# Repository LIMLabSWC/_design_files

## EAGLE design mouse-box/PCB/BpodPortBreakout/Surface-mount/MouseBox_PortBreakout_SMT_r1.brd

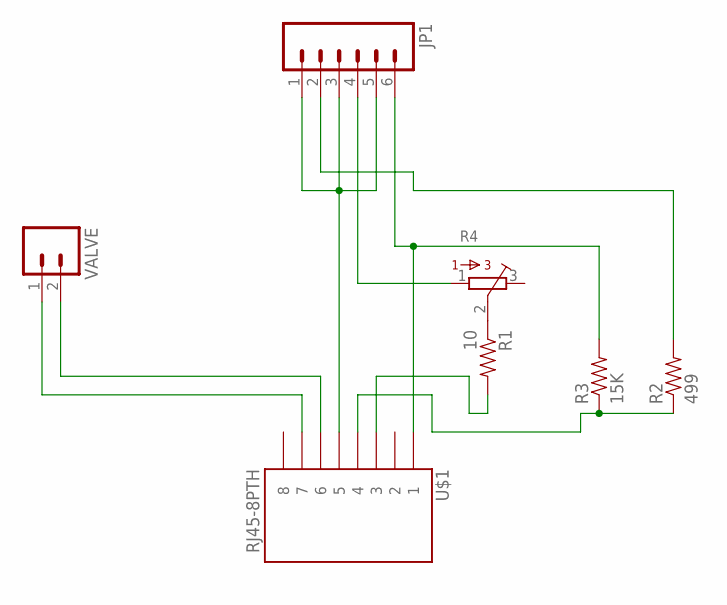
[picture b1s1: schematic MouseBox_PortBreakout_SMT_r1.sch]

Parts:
JP1: M063.5MM-6; SCREWTERMINAL-3.5MM-6
R1: 10; 1206
R2: 499; 1206
R3: 15K; 1206
R4: 3362R
U$1: RJ45-8PTH; RJ45-8
VALVE: M023.5MM_LOCK; SCREWTERMINAL-3.5MM-2_LOCK

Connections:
GND: JP1.1, JP1.3, JP1.5, U$1.5
unnamed: JP1.6, R3.2, U$1.1
unnamed: R2.1, R3.1, U$1.4
unnamed: JP1.2, R2.2
unnamed: R1.1, R4.2
unnamed: U$1.6, VALVE.2
unnamed: U$1.7, VALVE.1
unnamed: JP1.4, R4.1
unnamed: R1.2, U$1.3

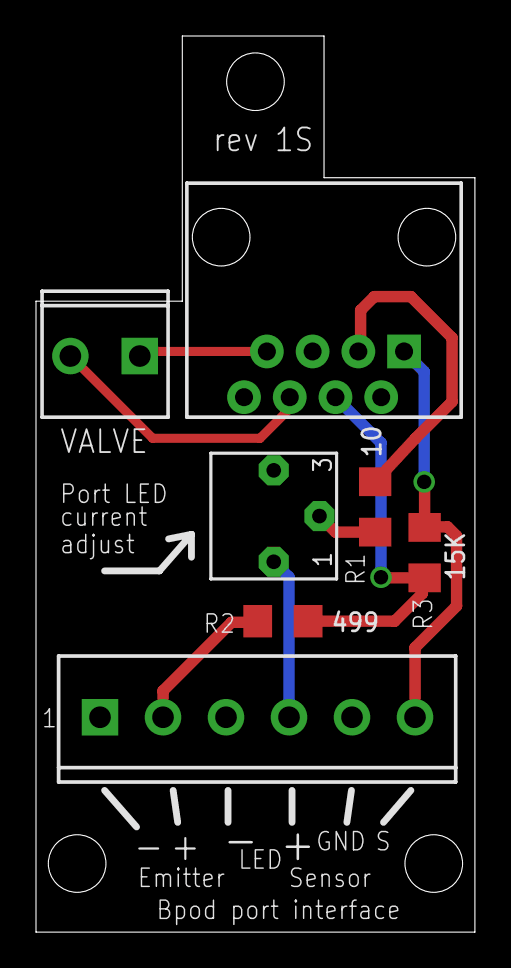
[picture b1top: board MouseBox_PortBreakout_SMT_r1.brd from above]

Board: 2 copper layers, 24.4 x 49.8 mm, 7 parts (0 on the bottom side), 9 nets.

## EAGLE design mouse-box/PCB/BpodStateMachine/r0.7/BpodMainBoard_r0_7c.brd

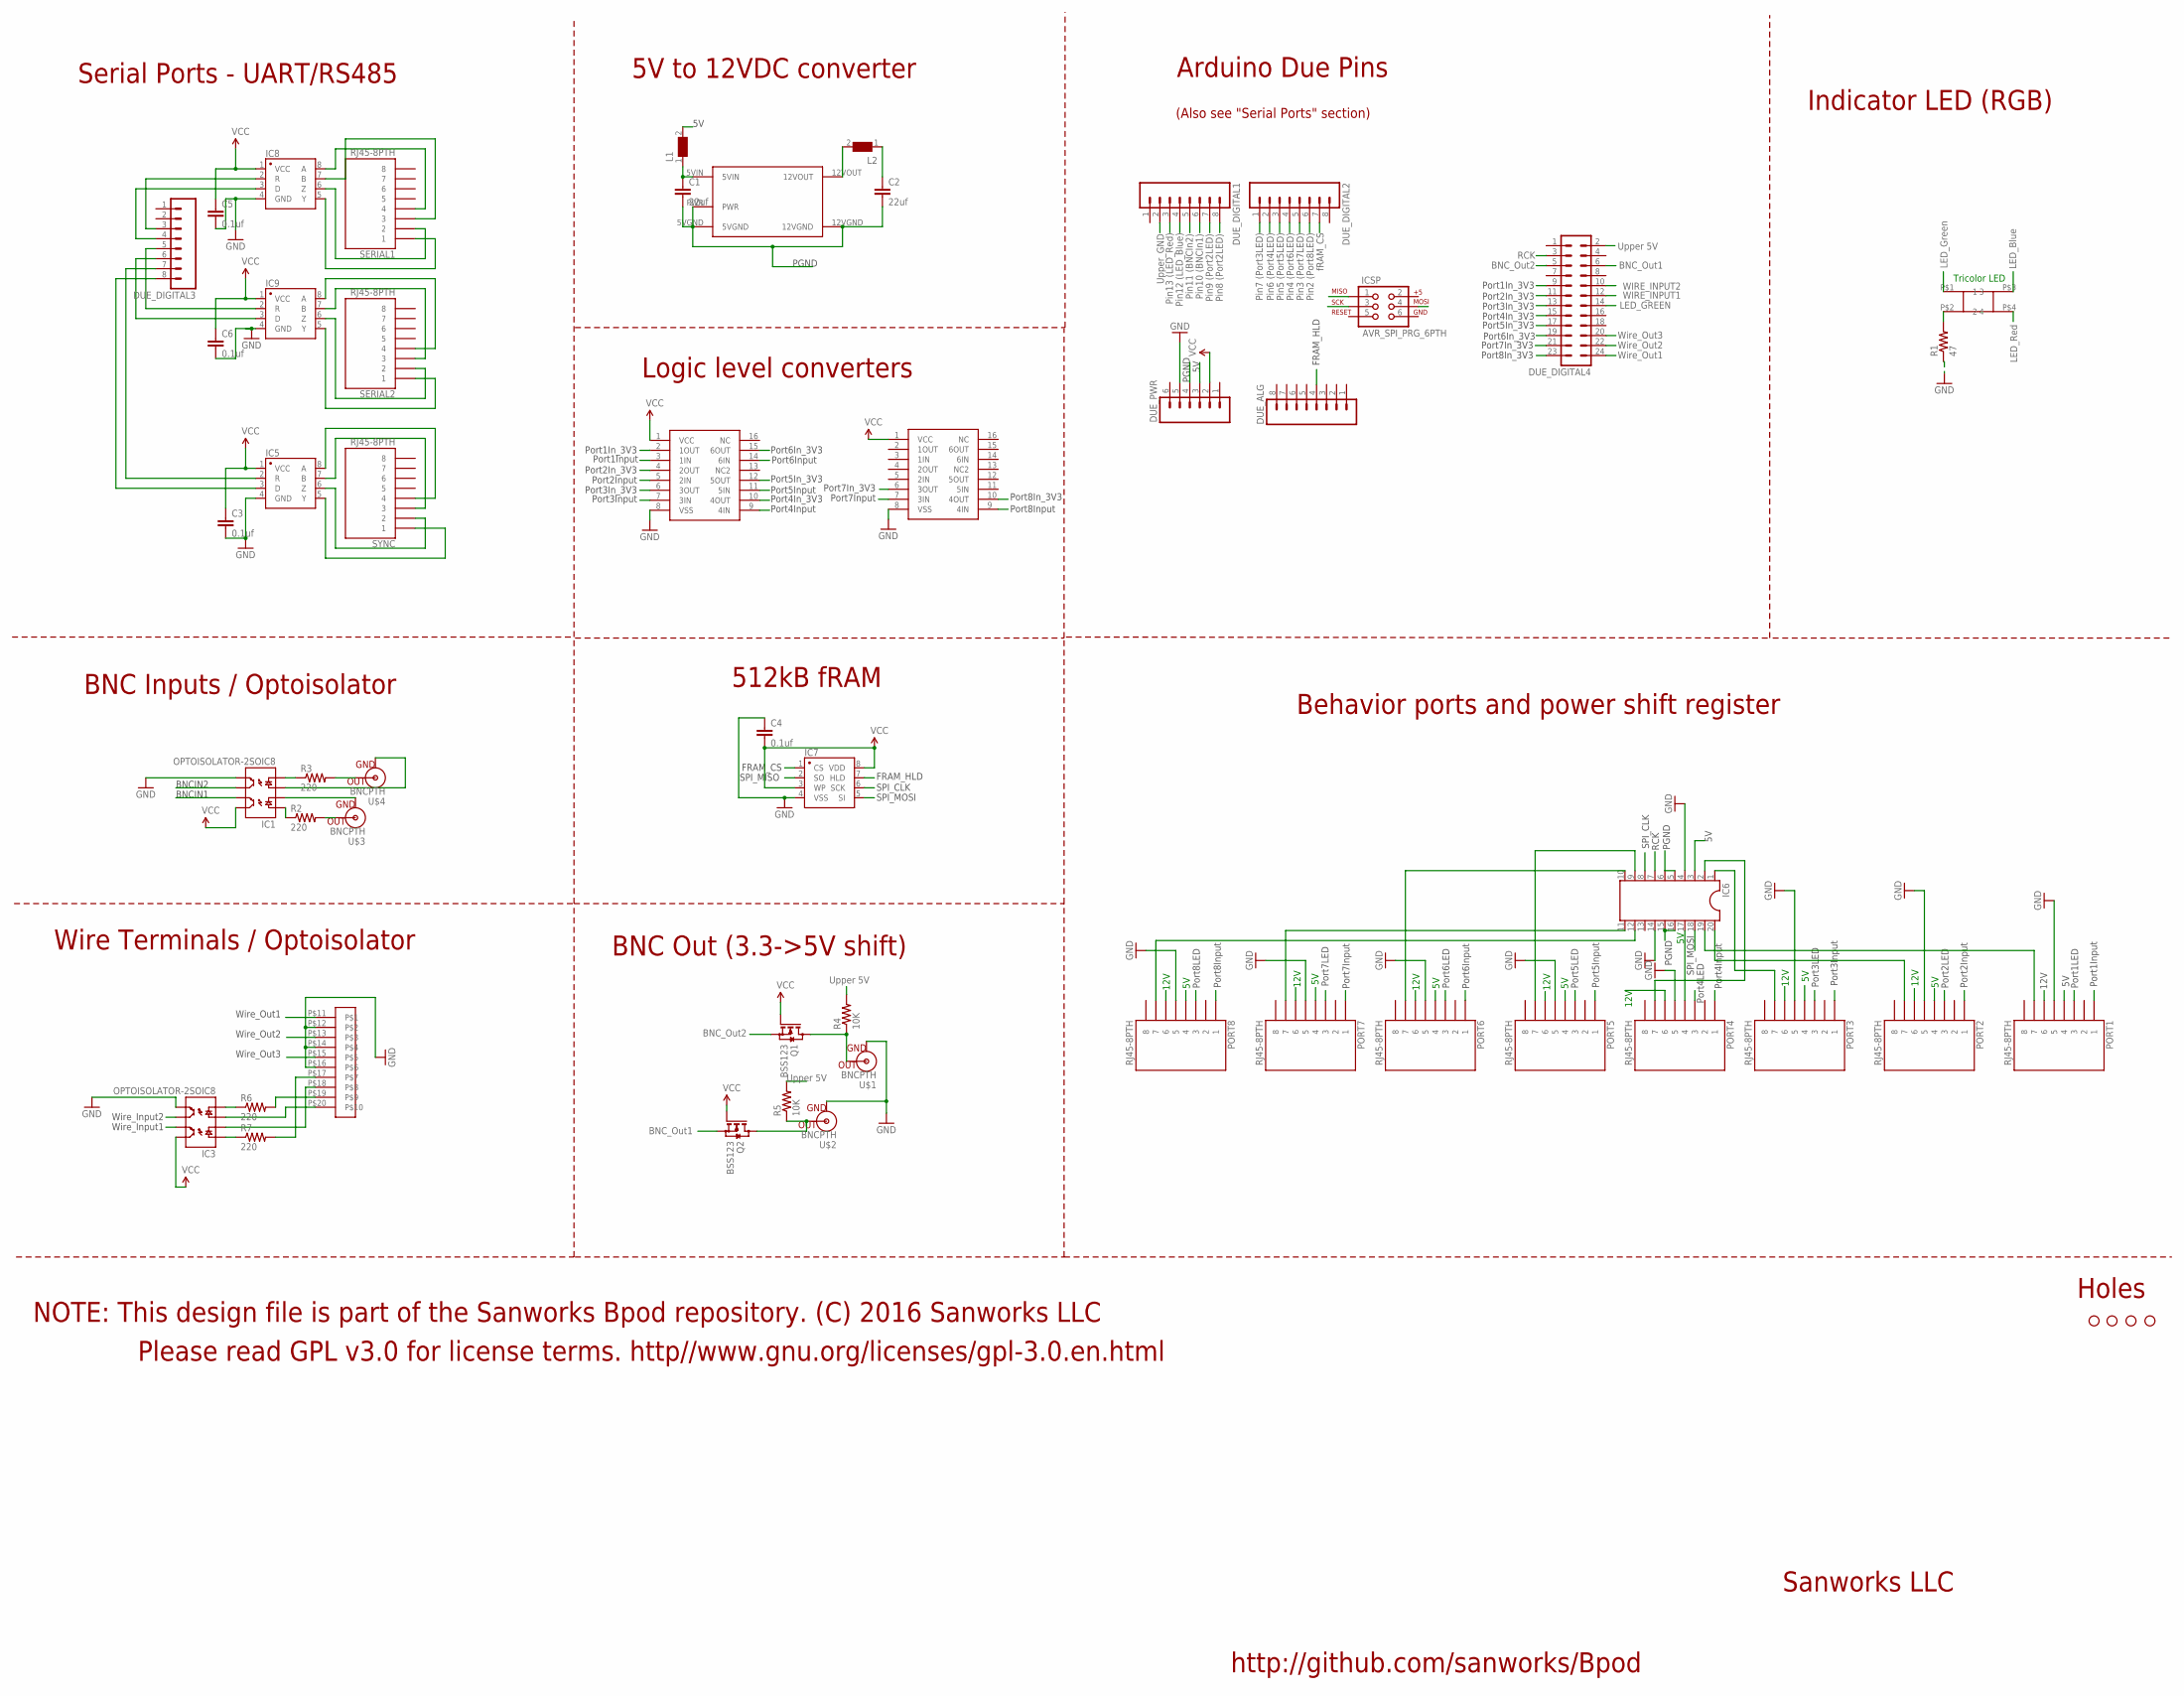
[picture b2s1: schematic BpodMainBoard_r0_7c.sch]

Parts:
C1, C2: 22uf; 1206
C3, C4, C5, C6: 0.1uf; 1206
DUE_ALG: M081X08; 1X08
DUE_DIGITAL1, DUE_DIGITAL2, DUE_DIGITAL3: M081X08; 1X08
DUE_DIGITAL4: MA12-2
DUE_PWR: M06SIP; 1X06
IC1, IC3: OPTOISOLATOR-2SOIC8; SO08-2
IC2, IC4: CD4050; SO16
IC5, IC8, IC9: SN65HVD31DR; SO08
IC6: DIL20
IC7: CY15B104Q-SXI; SO08-UNIVERSAL
ICSP: AVR_SPI_PRG_6PTH; 2X3
JP1, JP2, JP3, JP4: STAND-OFF
L1: WE-CBF-742792118_1206; 1206
L2: WE-CBF-742792118_1206; 1206; MPN 742792118
PORT1, PORT2, PORT3, PORT4, PORT5, PORT6, PORT7, PORT8: RJ45-8PTH; RJ45-8
Q1, Q2: BSS123; SOT23
R1: 47; 1206
R2, R3, R6, R7: 220; 1206
R4, R5: 10K; 1206
SERIAL1, SERIAL2: RJ45-8PTH; RJ45-8
SYNC: RJ45-8PTH; RJ45-8
U$1, U$2, U$3, U$4: BNCPTH; BNC
U$5: TDK_LAMBDA_5V_TO_12V; TDK_LAMBDA_5V_12V
U$6: 10POS_SPRING_TERMINAL; 10POS_SCREW_TERMINAL
U$8: SQUARE_TRICOLOR_LED

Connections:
5V: DUE_PWR.3, IC6.3, IC6.17, L1.2, PORT1.4, PORT2.4, PORT3.4, PORT4.4, PORT5.4, PORT6.4, PORT7.4, PORT8.4
12V: C2.1, L2.1, PORT1.6, PORT2.6, PORT3.6, PORT4.6, PORT5.6, PORT6.6, PORT7.6, PORT8.6
BNCIN1: DUE_DIGITAL1.6, IC1.7 (EM1)
BNCIN2: DUE_DIGITAL1.5, IC1.6 (CL2)
BNC_OUT1: DUE_DIGITAL4.6, Q2.2 (S)
BNC_OUT2: DUE_DIGITAL4.5, Q1.2 (S)
FRAM_CS: DUE_DIGITAL2.7, IC7.1 (CS)
FRAM_HLD: DUE_ALG.4, IC7.7 (HLD)
GND: C3.2, C5.2, C6.2, DUE_PWR.5, IC1.5 (EM2), IC2.8 (VSS), IC3.5 (EM2), IC4.8 (VSS), IC5.4 (GND), IC6.4, IC6.14, IC7.4 (VSS), IC8.4 (GND), IC9.4 (GND), PORT1.5, PORT2.5, PORT3.5, PORT4.5, PORT5.5, PORT6.5, PORT7.5, PORT8.5, R1.1, U$1.GND, U$2.GND, U$6.P$12, U$6.P$14, U$6.P$16
LED_BLUE: DUE_DIGITAL1.4, U$8.P$3 (3)
LED_GREEN: DUE_DIGITAL4.14, U$8.P$1 (1)
LED_RED: DUE_DIGITAL1.3, U$8.P$4 (4)
MOSI: IC6.18, IC7.5 (SI), ICSP.4
unnamed: R3.2, U$4.S (OUT)
unnamed: R2.2, U$3.S (OUT)
unnamed: IC1.3 (A2), U$4.GND
unnamed: IC1.2 (C1), U$3.GND
unnamed: R6.2, U$6.P$19
unnamed: Q1.3 (D), R4.1, U$1.S (OUT)
unnamed: Q2.3 (D), R5.1, U$2.S (OUT)
unnamed: IC6.19, PORT1.7
unnamed: IC6.20, PORT2.7
unnamed: IC6.1, PORT3.7
unnamed: IC6.2, PORT4.7
unnamed: IC6.9, PORT5.7
unnamed: IC6.10, PORT6.7
unnamed: IC6.11, PORT7.7
unnamed: IC6.12, PORT8.7
unnamed: IC5.8 (A), SYNC.4
unnamed: IC5.7 (B), SYNC.3
unnamed: IC5.6 (Z), SYNC.2
unnamed: IC5.5 (Y), SYNC.1
unnamed: DUE_DIGITAL3.7, IC5.2 (R)
unnamed: IC3.4 (C2), R6.1
unnamed: IC3.1 (A1), R7.1
unnamed: R1.2, U$8.P$2 (2)
unnamed: DUE_DIGITAL3.8, IC5.3 (D)
unnamed: IC8.8 (A), SERIAL1.4
unnamed: IC8.7 (B), SERIAL1.3
unnamed: IC8.6 (Z), SERIAL1.2
unnamed: IC8.5 (Y), SERIAL1.1
unnamed: IC9.8 (A), SERIAL2.4
unnamed: IC9.7 (B), SERIAL2.3
unnamed: IC9.6 (Z), SERIAL2.2
unnamed: IC9.5 (Y), SERIAL2.1
unnamed: DUE_DIGITAL3.3, IC8.2 (R)
unnamed: IC3.3 (A2), U$6.P$20
unnamed: R7.2, U$6.P$17
unnamed: IC3.2 (C1), U$6.P$18
unnamed: C1.1, L1.1, U$5.5VIN
unnamed: L2.2, U$5.12VOUT
unnamed: DUE_DIGITAL3.4, IC8.3 (D)
unnamed: DUE_DIGITAL3.5, IC9.2 (R)
unnamed: DUE_DIGITAL3.6, IC9.3 (D)
unnamed: IC1.1 (A1), R2.1
unnamed: IC1.4 (C2), R3.1
PGND: C1.2, C2.2, DUE_PWR.4, IC6.5, IC6.6, IC6.15, IC6.16, U$5.5VGND, U$5.12VGND, U$5.PWR
PORT1INPUT: IC4.3 (1IN), PORT1.1
PORT1IN_3V3: DUE_DIGITAL4.9, IC4.2 (1OUT)
PORT1LED: DUE_DIGITAL1.7, PORT1.3
PORT2INPUT: IC4.5 (2IN), PORT2.1
PORT2IN_3V3: DUE_DIGITAL4.11, IC4.4 (2OUT)
PORT2LED: DUE_DIGITAL1.8, PORT2.3
PORT3INPUT: IC4.7 (3IN), PORT3.1
PORT3IN_3V3: DUE_DIGITAL4.13, IC4.6 (3OUT)
PORT3LED: DUE_DIGITAL2.1, PORT3.3
PORT4INPUT: IC4.9 (4IN), PORT4.1
PORT4IN_3V3: DUE_DIGITAL4.15, IC4.10 (4OUT)
PORT4LED: DUE_DIGITAL2.2, PORT4.3
PORT5INPUT: IC4.11 (5IN), PORT5.1
PORT5IN_3V3: DUE_DIGITAL4.17, IC4.12 (5OUT)
PORT5LED: DUE_DIGITAL2.3, PORT5.3
PORT6INPUT: IC4.14 (6IN), PORT6.1
PORT6IN_3V3: DUE_DIGITAL4.19, IC4.15 (6OUT)
PORT6LED: DUE_DIGITAL2.4, PORT6.3
PORT7INPUT: IC2.7 (3IN), PORT7.1
PORT7IN_3V3: DUE_DIGITAL4.21, IC2.6 (3OUT)
PORT7LED: DUE_DIGITAL2.5, PORT7.3
PORT8INPUT: IC2.9 (4IN), PORT8.1
PORT8IN_3V3: DUE_DIGITAL4.23, IC2.10 (4OUT)
PORT8LED: DUE_DIGITAL2.6, PORT8.3
RCK: DUE_DIGITAL4.3, IC6.7
SPI_CLK: IC6.8, IC7.6 (SCK), ICSP.3
SPI_MISO: IC7.2 (SO), ICSP.1
UPPER_5V: DUE_DIGITAL4.2, R4.2, R5.2
UPPER_GND: DUE_DIGITAL1.2
VCC: C3.1, C4.2, C5.1, C6.1, DUE_PWR.2, IC1.8 (CL1), IC2.1 (VCC), IC3.8 (CL1), IC4.1 (VCC), IC5.1 (VCC), IC7.3 (WP), IC7.8 (VDD), IC8.1 (VCC), IC9.1 (VCC), Q1.1 (G), Q2.1 (G)
WIREOUT3: DUE_DIGITAL4.20, U$6.P$15
WIRE_INPUT1: DUE_DIGITAL4.12, IC3.7 (EM1)
WIRE_INPUT2: DUE_DIGITAL4.10, IC3.6 (CL2)
WIRE_OUT1: DUE_DIGITAL4.24, U$6.P$11
WIRE_OUT2: DUE_DIGITAL4.22, U$6.P$13

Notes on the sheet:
12V
Pin10 (BNCIn1)
Pin11 (BNCIn2)
Upper 5V
Tricolor LED
BNCIN1
BNCIN2
PGND
Pin12 (LED_Blue)
Pin13 (LED_Red)
Upper_GND
Pin8 (Port2LED)
Pin9 (Port2LED)
Pin7 (Port3LED)
Pin6 (Port4LED)
Pin5 (Port5LED)
Pin4 (Port6LED)
Pin3 (Port7LED)
Pin2 (Port8LED)
fRAM_CS
Port1LED
Serial Ports - UART/RS485
BNC Inputs / Optoisolator
Port2LED
5V to 12VDC converter
Sanworks LLC
Port3LED
Port4LED
Port5LED
Port6LED
Port7LED
Port8LED
Logic level converters
Port1Input
Port2Input
Port3Input
Port4Input
Port5Input
Port6Input
Port7Input

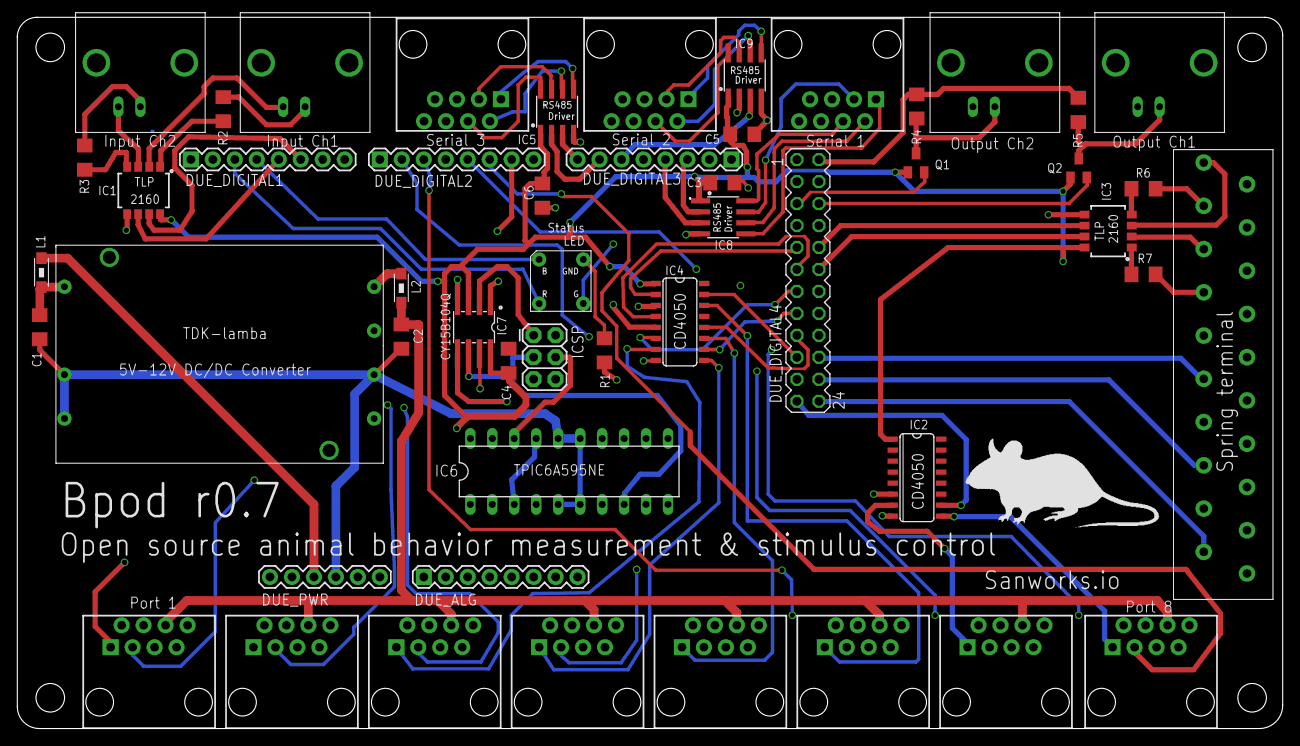
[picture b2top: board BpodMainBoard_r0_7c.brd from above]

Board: 4 copper layers, 146.3 x 82.2 mm, 56 parts (0 on the bottom side), 91 nets.

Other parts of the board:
U$7: MOUSELOGO

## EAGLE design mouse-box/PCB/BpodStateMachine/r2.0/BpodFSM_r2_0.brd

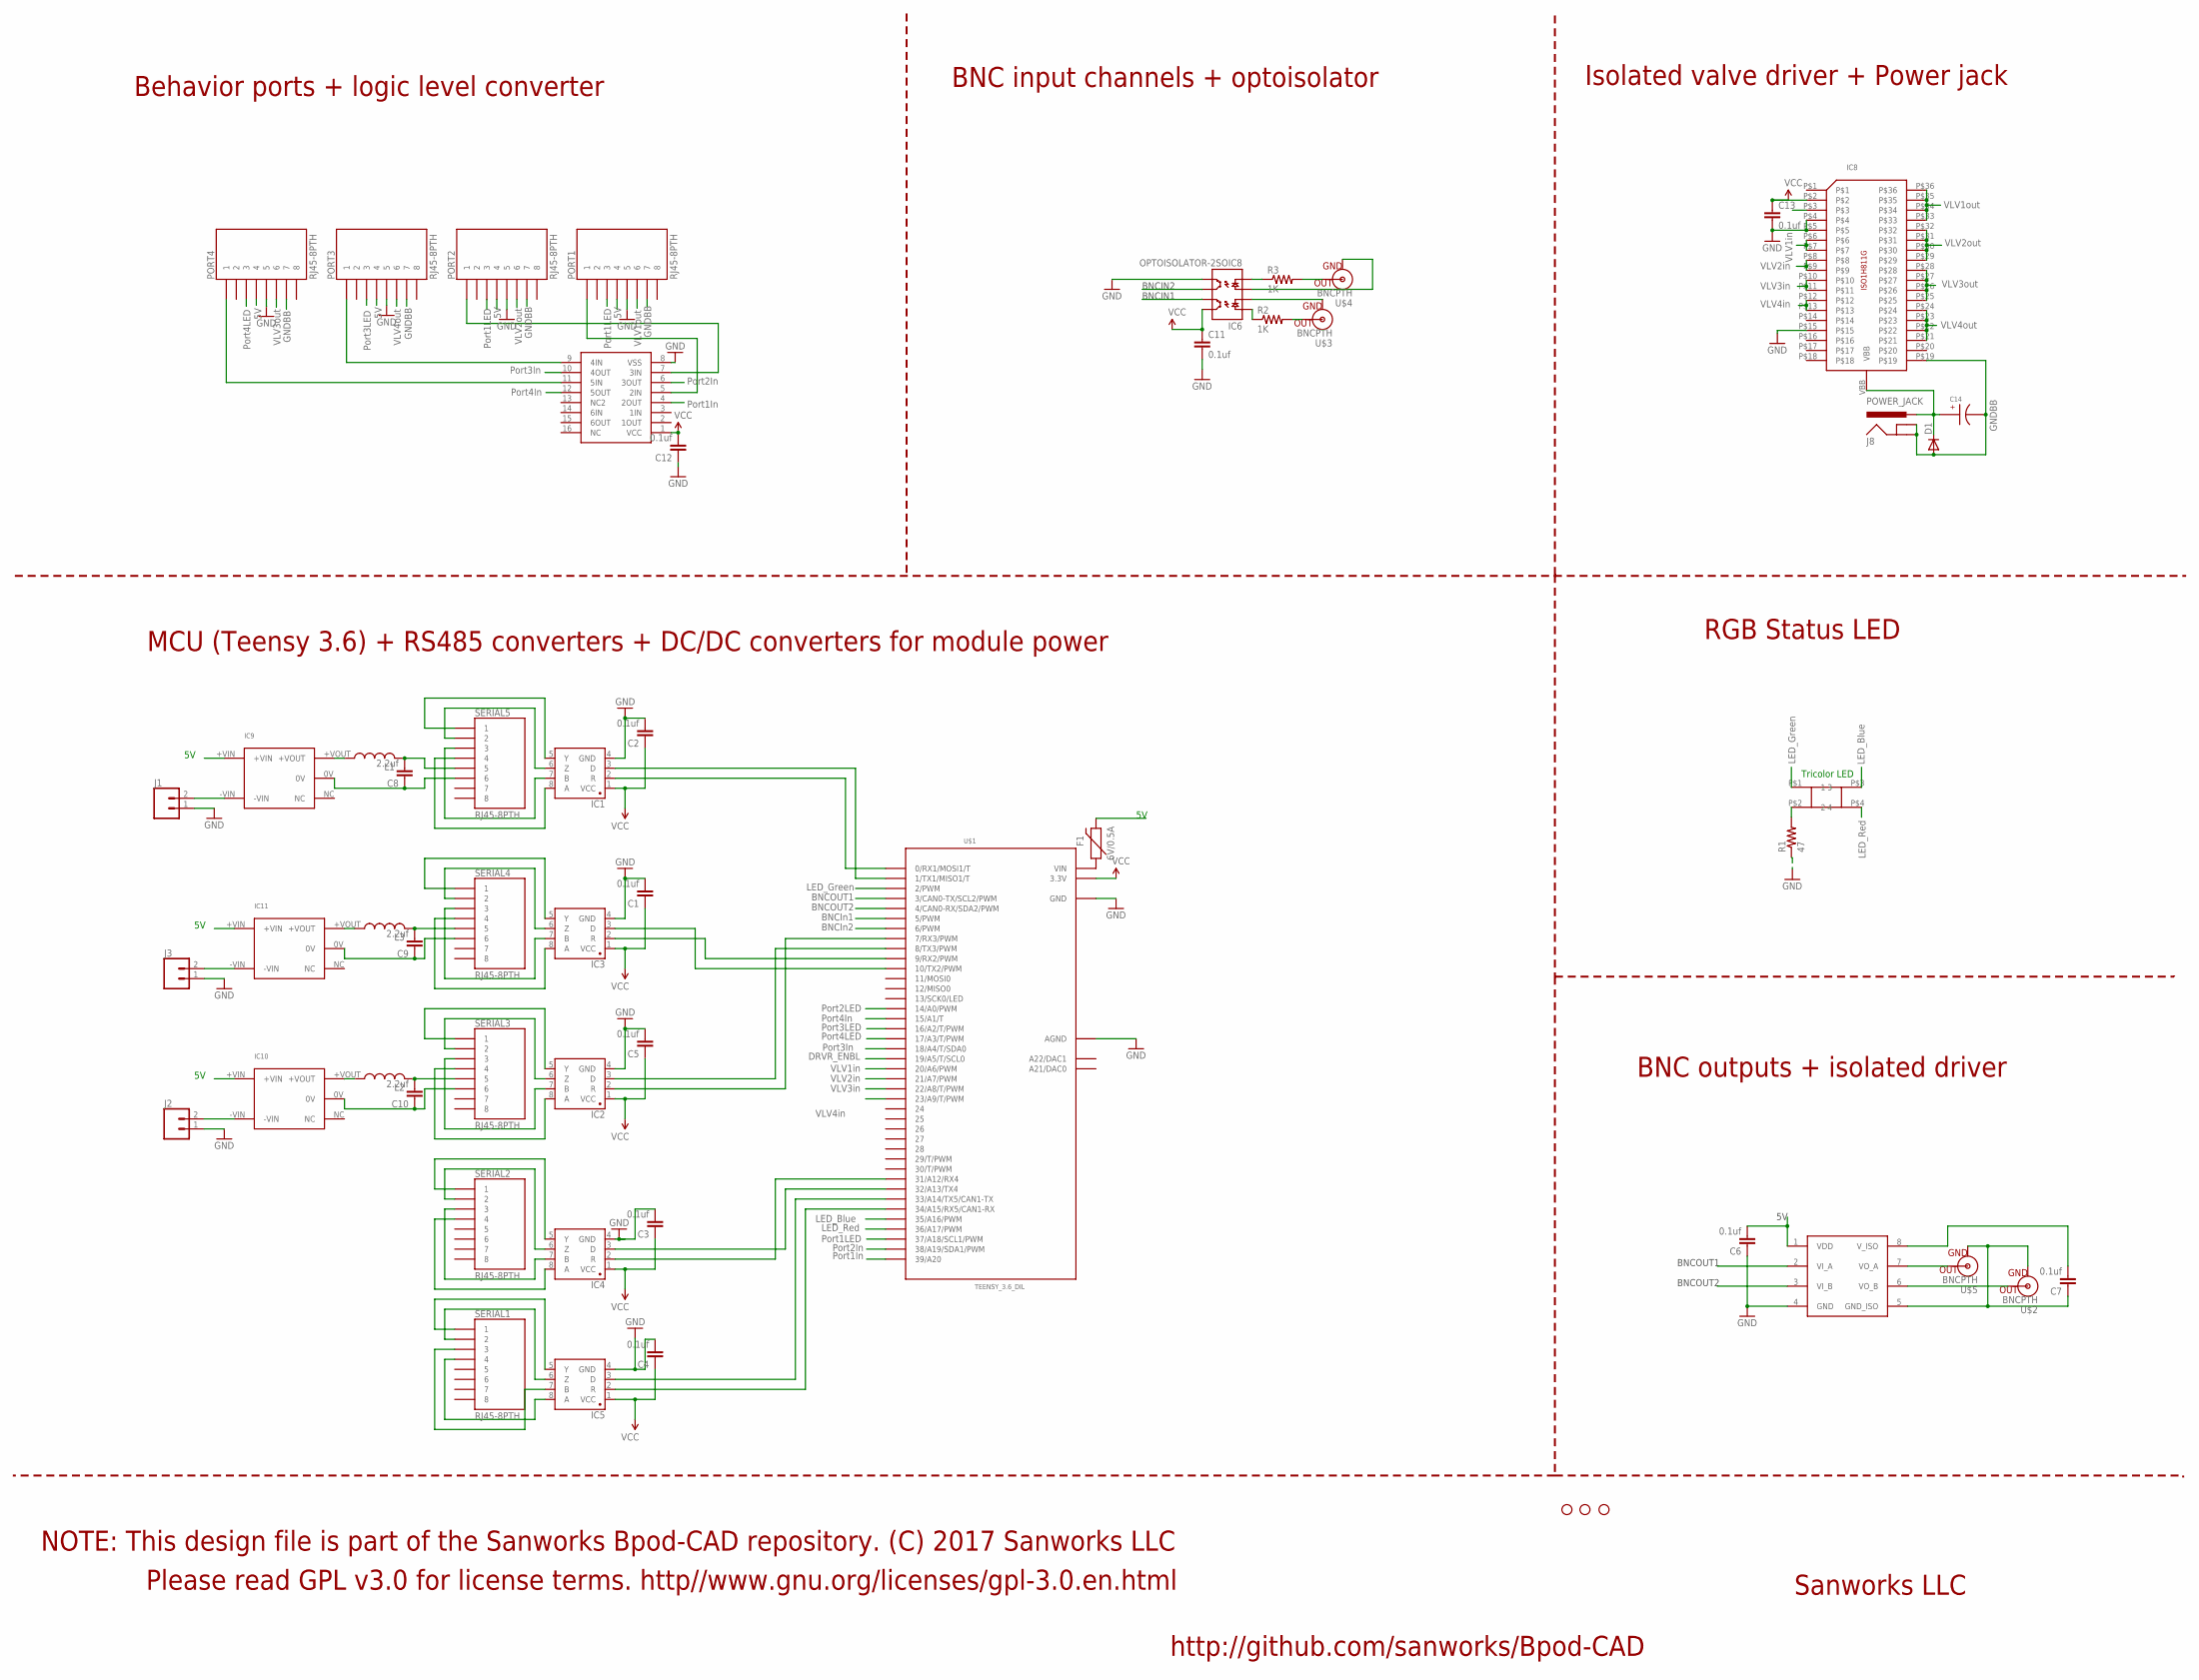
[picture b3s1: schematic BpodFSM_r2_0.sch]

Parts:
C1, C2, C3, C4, C5, C6, C7, C11, C12, C13: 0.1uf; 1206
C8, C9, C10: 2.2uf; 1206
C14: EEE-FK1H100UR
D1: DIODE-DO214AA; DO214AA
F1: 6V/0.5A; 1206
IC1, IC2, IC3, IC4, IC5: SN65HVD31DR; SO08
IC6: OPTOISOLATOR-2SOIC8; SO08-2
IC7: ADUM5240; SO08
IC8: ISO1H811G
IC9, IC10, IC11: MTU1D0505MC
IC12: CD4050; SO16
J1, J2, J3: CONN_02; 1X02
J8: POWER_JACK; POWER_JACK_PTH
JP3, JP4, JP5: STAND-OFF
L1, L2, L3: L-USL3225M; L3225M
PORT1, PORT2, PORT3, PORT4: RJ45-8PTH; RJ45-8
R1: 47; 1206
R2, R3: 1K; 1206
SERIAL1, SERIAL2, SERIAL3, SERIAL4, SERIAL5: RJ45-8PTH; RJ45-8
U$1: TEENSY_3.6_DIL
U$2, U$3, U$4, U$5: BNCPTH; BNC
U$8: SQUARE_TRICOLOR_LED

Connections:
5V: C6.2, F1.2, IC7.1 (VDD), IC9.+VIN, IC10.+VIN, IC11.+VIN, PORT1.4, PORT2.4, PORT3.4, PORT4.4
BNCIN1: IC6.7 (EM1), U$1.6 (6/PWM)
BNCIN2: IC6.6 (CL2), U$1.5 (5/PWM)
BNCOUT1: IC7.3 (VI_B), U$1.4 (4/CAN0-RX/SDA2/PWM)
BNCOUT2: IC7.2 (VI_A), U$1.3 (3/CAN0-TX/SCL2/PWM)
DRVR_ENBL: IC8.P$3, U$1.19/A5 (19/A5/T/SCL0)
GND: C1.2, C2.2, C3.2, C4.2, C5.2, C6.1, C11.2, C12.1, C13.2, IC1.4 (GND), IC2.4 (GND), IC3.4 (GND), IC4.4 (GND), IC5.4 (GND), IC6.5 (EM2), IC7.4 (GND), IC8.P$4, IC8.P$5, IC8.P$15, IC12.8 (VSS), J1.1, J2.1, J3.1, PORT1.5, PORT2.5, PORT3.5, PORT4.5, R1.1, U$1.AGND, U$1.GND, U$1.GND1 (GND)
GNDBB: C14.CATHODE, D1.A, IC8.P$19, J8.GND, J8.GNDBREAK, PORT1.7, PORT2.7, PORT3.7, PORT4.7
ISOGND: C7.1, IC7.5 (GND_ISO), U$2.GND, U$5.GND
LED_BLUE: U$1.35/A16 (35/A16/PWM), U$8.P$3 (3)
LED_GREEN: U$1.2 (2/PWM), U$8.P$1 (1)
LED_RED: U$1.36/A17 (36/A17/PWM), U$8.P$4 (4)
unnamed: IC3.8 (A), SERIAL4.4
unnamed: IC3.7 (B), SERIAL4.3
unnamed: IC3.6 (Z), SERIAL4.2
unnamed: IC3.5 (Y), SERIAL4.1
unnamed: IC3.2 (R), U$1.9 (9/RX2/PWM)
unnamed: IC3.3 (D), U$1.10 (10/TX2/PWM)
unnamed: IC1.8 (A), SERIAL5.4
unnamed: IC1.7 (B), SERIAL5.3
unnamed: IC1.6 (Z), SERIAL5.2
unnamed: IC1.5 (Y), SERIAL5.1
unnamed: IC1.2 (R), U$1.0 (0/RX1/MOSI1/T)
unnamed: IC1.3 (D), U$1.1 (1/TX1/MISO1/T)
unnamed: IC6.3 (A2), U$4.GND
unnamed: R3.2, U$4.S (OUT)
unnamed: R2.2, U$3.S (OUT)
unnamed: IC6.2 (C1), U$3.GND
unnamed: IC2.8 (A), SERIAL3.4
unnamed: IC2.7 (B), SERIAL3.3
unnamed: IC2.6 (Z), SERIAL3.2
unnamed: IC12.7 (3IN), PORT2.1
unnamed: IC2.5 (Y), SERIAL3.1
unnamed: IC2.2 (R), U$1.7 (7/RX3/PWM)
unnamed: C8.2, L1.2, SERIAL5.5
unnamed: IC12.9 (4IN), PORT3.1
unnamed: R1.2, U$8.P$2 (2)
unnamed: C8.1, IC9.0V, SERIAL5.6
unnamed: IC7.7 (VO_A), U$5.S (OUT)
unnamed: IC2.3 (D), U$1.8 (8/TX3/PWM)
unnamed: F1.1, U$1.VIN
unnamed: IC7.6 (VO_B), U$2.S (OUT)
unnamed: IC12.11 (5IN), PORT4.1
unnamed: IC5.8 (A), SERIAL1.4
unnamed: IC5.7 (B), SERIAL1.3
unnamed: IC5.6 (Z), SERIAL1.2
unnamed: IC5.5 (Y), SERIAL1.1
unnamed: IC4.8 (A), SERIAL2.4
unnamed: IC4.7 (B), SERIAL2.3
unnamed: IC4.6 (Z), SERIAL2.2
unnamed: IC9.+VOUT, L1.1
unnamed: IC4.5 (Y), SERIAL2.1
unnamed: IC9.-VIN, J1.2
unnamed: IC5.2 (R), U$1.34/A15 (34/A15/RX5/CAN1-RX)
unnamed: C10.1, IC10.0V, SERIAL3.6
unnamed: C10.2, L2.2, SERIAL3.5
unnamed: IC10.+VOUT, L2.1
unnamed: IC10.-VIN, J2.2
unnamed: C9.1, IC11.0V, SERIAL4.6
unnamed: IC5.3 (D), U$1.33/A14 (33/A14/TX5/CAN1-TX)
unnamed: C9.2, L3.2, SERIAL4.5
unnamed: IC11.+VOUT, L3.1
unnamed: IC11.-VIN, J3.2
unnamed: IC4.2 (R), U$1.31/A12 (31/A12/RX4)
unnamed: IC4.3 (D), U$1.32/A13 (32/A13/TX4)
unnamed: IC6.1 (A1), R2.1
unnamed: IC6.4 (C2), R3.1
unnamed: IC12.5 (2IN), PORT1.1
unnamed: C7.2, IC7.8 (V_ISO)
PORT1IN: IC12.4 (2OUT), U$1.39/A20
PORT1LED: PORT1.3, U$1.37/A18 (37/A18/SCL1/PWM)
PORT2IN: IC12.6 (3OUT), U$1.38/A19 (38/A19/SDA1/PWM)
PORT2LED: PORT2.3, U$1.14/A0 (14/A0/PWM)
PORT3IN: IC12.10 (4OUT), U$1.18/A4 (18/A4/T/SDA0)
PORT3LED: PORT3.3, U$1.16/A2 (16/A2/T/PWM)
PORT4IN: IC12.12 (5OUT), U$1.15/A1 (15/A1/T)
PORT4LED: PORT4.3, U$1.17/A3 (17/A3/T/PWM)
VBB: C14.ANODE, D1.C, IC8.VBB, J8.PWR
VCC: C1.1, C2.1, C3.1, C4.1, C5.1, C11.1, C12.2, C13.1, IC1.1 (VCC), IC2.1 (VCC), IC3.1 (VCC), IC4.1 (VCC), IC5.1 (VCC), IC6.8 (CL1), IC8.P$2, IC12.1 (VCC), U$1.3.3V, U$1.3.3V3 (3.3V)
VLV1IN: IC8.P$6, IC8.P$7, U$1.23/A9 (23/A9/T/PWM)
VLV1OUT: IC8.P$33, IC8.P$34, IC8.P$35, IC8.P$36, PORT1.6
VLV2IN: IC8.P$8, IC8.P$9, U$1.22/A8 (22/A8/T/PWM)
VLV2OUT: IC8.P$29, IC8.P$30, IC8.P$31, IC8.P$32, PORT2.6
VLV3IN: IC8.P$12, IC8.P$13, U$1.20/A6 (20/A6/PWM)
VLV3OUT: IC8.P$21, IC8.P$22, IC8.P$23, IC8.P$24, PORT3.6
VLV4IN: IC8.P$10, IC8.P$11, U$1.21/A7 (21/A7/PWM)
VLV4OUT: IC8.P$25, IC8.P$26, IC8.P$27, IC8.P$28, PORT4.6

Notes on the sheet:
Tricolor LED
LED_Blue
LED_Red
LED_Green
BNCIN1
BNCIN2
BNCIn1
BNCIn2
BNCOUT2
BNCOUT1
Port1In
Port2In
Port3In
Port4In
Port1LED
Port2LED
Port3LED
Port4LED
DRVR_ENBL
VLV2in
VLV3in
VLV4in
VLV1in
GNDBB
VLV1out
VLV2out
VLV3out
VLV4out
Sanworks LLC
http://github.com/sanworks/Bpod-CAD
Please read GPL v3.0 for license terms. http//www.gnu.org/licenses/gpl-3.0.en.html
NOTE: This design file is part of the Sanworks Bpod-CAD repository. (C) 2017 Sanworks LLC
Behavior ports + logic level converter
BNC input channels + optoisolator
Isolated valve driver + Power jack
RGB Status LED
BNC outputs + isolated driver
MCU (Teensy 3.6) + RS485 converters + DC/DC converters for module power

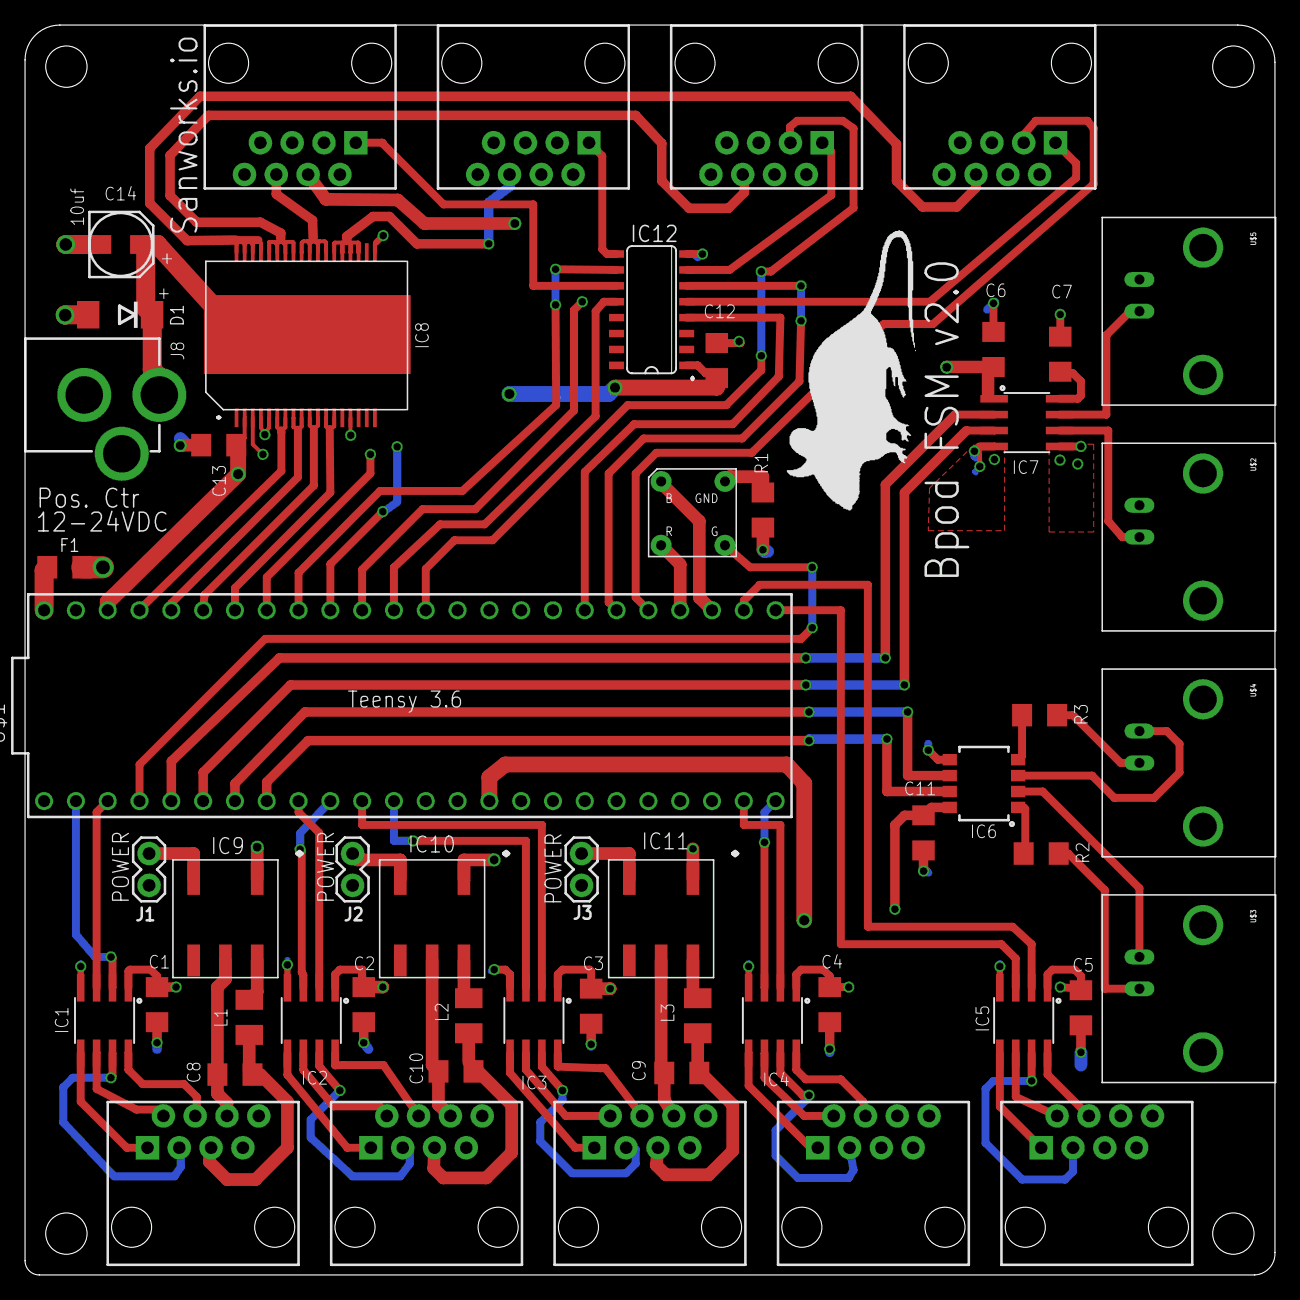
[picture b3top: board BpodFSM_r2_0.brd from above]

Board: 4 copper layers, 99.8 x 99.8 mm, 58 parts (0 on the bottom side), 87 nets.

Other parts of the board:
JP1: STAND-OFF
U$9: MOUSELOGO

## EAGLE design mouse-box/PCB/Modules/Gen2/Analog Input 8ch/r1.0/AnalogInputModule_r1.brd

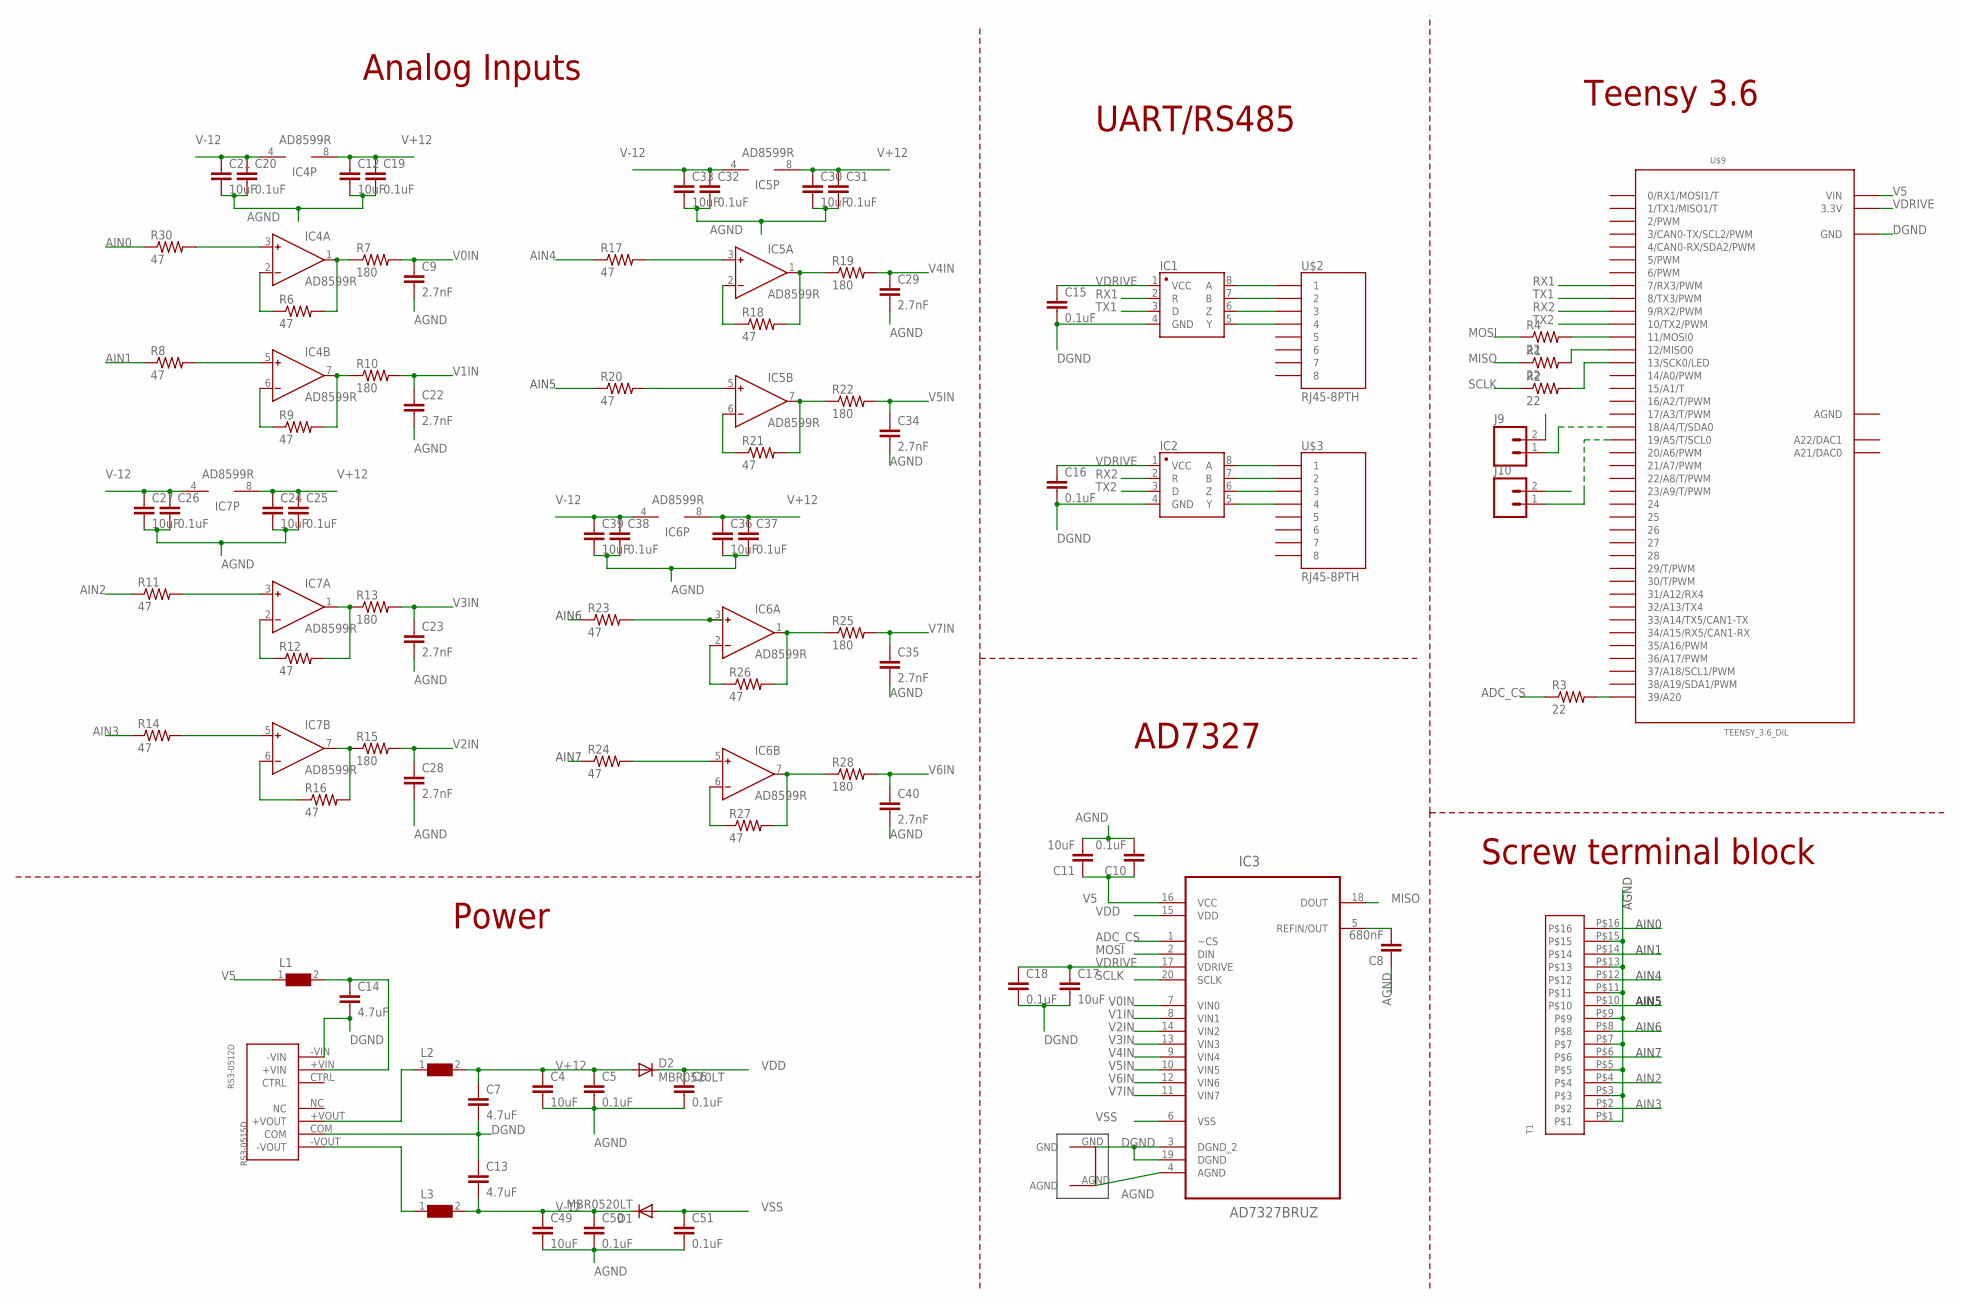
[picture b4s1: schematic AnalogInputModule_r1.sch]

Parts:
C4, C11, C12, C17, C21, C24, C27, C30, C33, C36, C39, C49: 10uF; 0805
C5, C6, C10, C15, C16, C18, C19, C20, C25, C26, C31, C32, C37, C38, C50, C51: 0.1uF; 0805
C7, C13, C14: 4.7uF; 1206
C8: 680nF; 0805
C9, C22, C23, C28, C29, C34, C35, C40: 2.7nF; 0805
D1, D2: MBR0520LT; SOD123
IC1, IC2: SN65HVD31DR; SO08
IC3: AD7327BRUZ; SOP65P640X120-20N
IC4, IC5, IC6, IC7: AD8599R; SO8
J9, J10: M023.5MM; SCREWTERMINAL-3.5MM-2
L1, L2, L3: WE-CBF-742792118_1206; 1206
R1, R2, R3, R4: 22; R0805
R6, R8, R9, R11, R12, R14, R16, R17, R18, R20, R21, R23, R24, R26, R27, R30: 47; R0805
R7, R10, R13, R15, R19, R22, R25, R28: 180; R0805
RS3-0512D: RS3-0515D
T1: 16POS_SCREWTERMINAL
U$2, U$3: RJ45-8PTH; RJ45-8
U$4: GNDPLANESHRT
U$9: TEENSY_3.6_DIL

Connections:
+VOUT: L2.1, RS3-0512D.+VOUT
-VOUT: L3.1, RS3-0512D.-VOUT
ADC_CS: IC3.1 (~CS), R3.1
AGND: C4.2, C5.2, C6.2, C8.1, C9.2, C10.2, C11.2, C12.2, C19.2, C20.2, C21.2, C22.2, C23.2, C24.2, C25.2, C26.2, C27.2, C28.2, C29.2, C30.2, C31.2, C32.2, C33.2, C34.2, C35.2, C36.2, C37.2, C38.2, C39.2, C40.2, C49.2, C50.2, C51.2, IC3.4 (AGND), T1.P$1, T1.P$3, T1.P$5, T1.P$7, T1.P$9, T1.P$11, T1.P$13, T1.P$15, U$4.AGND, U$9.AGND
AIN0: R30.1, T1.P$16
AIN1: R8.1, T1.P$14
AIN2: R11.1, T1.P$4
AIN3: R14.1, T1.P$2
AIN4: R17.1, T1.P$12
AIN5: R20.1, T1.P$10
AIN6: R23.1, T1.P$8
AIN7: R24.1, T1.P$6
DGND: C7.2, C13.1, C14.2, C15.2, C16.2, C17.2, C18.2, IC1.4 (GND), IC2.4 (GND), IC3.3 (DGND_2), IC3.19 (DGND), J9.2, J10.2, RS3-0512D.-VIN, RS3-0512D.COM, U$4.GND, U$9.GND, U$9.GND1 (GND)
MISO: IC3.18 (DOUT), R1.1
MOSI: IC3.2 (DIN), R4.1
unnamed: IC1.6 (Z), U$2.3
unnamed: IC1.8 (A), U$2.1
unnamed: IC1.5 (Y), U$2.4
unnamed: IC1.7 (B), U$2.2
unnamed: IC2.6 (Z), U$3.3
unnamed: IC2.5 (Y), U$3.4
unnamed: IC2.8 (A), U$3.1
unnamed: IC2.7 (B), U$3.2
unnamed: R4.2, U$9.11 (11/MOSI0)
unnamed: R1.2, U$9.12 (12/MISO0)
unnamed: C14.1, L1.2, RS3-0512D.+VIN
unnamed: R3.2, U$9.39/A20
unnamed: IC4.3 (IN+), R30.2
unnamed: R2.2, U$9.13 (13/SCK0/LED)
unnamed: IC4.2 (IN-), R6.1
unnamed: IC4.1 (OUT), R6.2, R7.1
unnamed: J9.1, U$9.18/A4 (18/A4/T/SDA0)
unnamed: J10.1, U$9.19/A5 (19/A5/T/SCL0)
unnamed: IC4.5 (IN+), R8.2
unnamed: IC4.6 (IN-), R9.1
unnamed: IC4.7 (OUT), R9.2, R10.1
unnamed: IC7.3 (IN+), R11.2
unnamed: IC7.2 (IN-), R12.1
unnamed: IC7.1 (OUT), R12.2, R13.1
unnamed: IC7.5 (IN+), R14.2
unnamed: IC7.6 (IN-), R16.1
unnamed: IC7.7 (OUT), R15.1, R16.2
unnamed: IC5.3 (IN+), R17.2
unnamed: IC5.2 (IN-), R18.1
unnamed: IC5.1 (OUT), R18.2, R19.1
unnamed: IC5.5 (IN+), R20.2
unnamed: IC5.6 (IN-), R21.1
unnamed: IC5.7 (OUT), R21.2, R22.1
unnamed: IC6.3 (IN+), R23.2
unnamed: IC6.2 (IN-), R26.1
unnamed: IC6.1 (OUT), R25.1, R26.2
unnamed: IC6.5 (IN+), R24.2
unnamed: IC6.6 (IN-), R27.1
unnamed: IC6.7 (OUT), R27.2, R28.1
REF: C8.2, IC3.5 (REFIN/OUT)
RX1: IC1.2 (R), U$9.7 (7/RX3/PWM)
RX2: IC2.2 (R), U$9.9 (9/RX2/PWM)
SCLK: IC3.20 (SCLK), R2.1
TX1: IC1.3 (D), U$9.8 (8/TX3/PWM)
TX2: IC2.3 (D), U$9.10 (10/TX2/PWM)
V0IN: C9.1, IC3.7 (VIN0), R7.2
V1IN: C22.1, IC3.8 (VIN1), R10.2
V2IN: C28.1, IC3.14 (VIN2), R15.2
V3IN: C23.1, IC3.13 (VIN3), R13.2
V4IN: C29.1, IC3.9 (VIN4), R19.2
V5: C10.1, C11.1, IC3.16 (VCC), L1.1, U$9.VIN
V5IN: C34.1, IC3.10 (VIN5), R22.2
V6IN: C40.1, IC3.12 (VIN6), R28.2
V7IN: C35.1, IC3.11 (VIN7), R25.2
V+12: C4.1, C5.1, C7.1, C12.1, C19.1, C24.1, C25.1, C30.1, C31.1, C36.1, C37.1, D2.A, IC4.8 (V+), IC5.8 (V+), IC6.8 (V+), IC7.8 (V+), L2.2
V-12: C13.2, C20.1, C21.1, C26.1, C27.1, C32.1, C33.1, C38.1, C39.1, C49.1, C50.1, D1.C, IC4.4 (V-), IC5.4 (V-), IC6.4 (V-), IC7.4 (V-), L3.2
VDD: C6.1, D2.C, IC3.15 (VDD)
VDRIVE: C15.1, C16.1, C17.1, C18.1, IC1.1 (VCC), IC2.1 (VCC), IC3.17 (VDRIVE), U$9.3.3V, U$9.3.3V3 (3.3V)
VSS: C51.1, D1.A, IC3.6 (VSS)

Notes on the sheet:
Teensy 3.6
UART/RS485
AD7327
Analog Inputs
Power
Screw terminal block
AIN7
AIN6
AIN5
AIN4
AIN1
AIN0
AGND

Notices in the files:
mouse-box/PCB/BpodStateMachine/r0.7/BpodMainBoard_r0_7c.sch:
NOTE: This design file is part of the Sanworks Bpod repository. (C) 2016 Sanworks LLC
parts and their libraries:
SparkFun-Resistors: Licensing: Creative Commons ShareAlike 4.0 International - https://creativecommons.org/licenses/by-sa/4.0
SparkFun-Passives: Licensing: CC v3.0 Share-Alike You are welcome to use this library for commercial purposes.
